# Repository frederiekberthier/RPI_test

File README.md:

# Raspberry Pi testsoftware
Test library om RPI hardwarematig te testen

## Opstelling
- **TEST-SERVER** (eigen Pi 5, met scherm): stuurt de test aan en maakt het rapport.
- **TEST-CLIENT** (de te testen Pi 4/5): bootet van een eigen TEST-CLIENT-SD met de agent.
- Verbonden met: GPIO-adapter (alleen GND + GPIO's, met serieweerstanden, géén 5V/3V3) en een
  rechtstreekse netwerkkabel met statische IP's. De GPIO-adapter kan op breadboards ([docs/opstelling.md](docs/opstelling.md)) of als
  print met één koperlaag ([docs/pcb.md](docs/pcb.md)).

**Namen:** de twee Pi's heten **TEST-SERVER** en **TEST-CLIENT**. Aan de scripts geef je `server` of `client` mee
(`./install.sh server`); de hostnamen worden `test-server` en `test-client`. De namen gaan over de Pi's, niet over het
netwerkprotocol: de agent op de TEST-CLIENT is technisch een HTTP-server en de TEST-SERVER roept hem aan.
"Raspberry Pi tester" is de naam van de applicatie.

## Installeren op een Pi: stappenplan
Eén script (`install.sh`) doet alles: voorcontrole, pakketten (`apt`), software, hostnaam, vrije GPIO-pinnen, wifi-land,
scherm met kiosk (TEST-SERVER), dienst en het vaste IP-adres. Het controleert per onderdeel eerst of het er al staat, dus je
kunt het veilig opnieuw uitvoeren. De stappen zijn voor de TEST-SERVER en de TEST-CLIENT-SD hetzelfde; alleen `server` of `client` verschilt.

1. **Schrijf Raspberry Pi OS Trixie (64-bit)** naar een SD-kaart met Raspberry Pi Imager: *met bureaublad* voor de TEST-SERVER,
   *Lite* voor de TEST-CLIENT-SD. Stel in de Imager een gebruiker, wifi (land `BE`) en SSH in.
2. **Start de Pi met internet** (via wifi, niet via de ethernetpoort die de testkabel wordt) en haal de software binnen:
   ```
   sudo apt install -y git
   git clone https://github.com/frederiekberthier/RPI_test.git
   cd RPI_test
   ```
3. **Kijk wat er al op de Pi staat** (optioneel, wijzigt niets):
   ```
   sudo ./install.sh server --check        # of: client
   ```
4. **Installeer** (voor het eerst ca. 5 tot 10 minuten):
   ```
   sudo ./install.sh server                # of: client
   ```
   Het script doet eerst een voorcontrole en stopt met een duidelijke melding als er iets ontbreekt.
5. **Herstart:** `sudo reboot`
6. **Controleer het resultaat:** `sudo ./image/verify.sh server` (of `client`)
7. **Iets mis?** `sudo ./image/diagnose.sh` verzamelt alle relevante uitvoer in één bestand om te delen.

| Optie | Wat het doet |
|---|---|
| `--check` | toont per onderdeel *aanwezig*, *ontbreekt* of *onbekend*; wijzigt niets |
| `--force` | past alles opnieuw toe, ook wat al aanwezig lijkt |
| `--readonly` | (alleen `client`) maakt het bestandssysteem alleen-lezen na de installatie |
| `--skip-preflight` | slaat de voorcontrole over |

**Bijwerken** naar een nieuwe versie: `git pull && sudo ./install.sh server`. Het script ziet dat alleen de software
verouderd is, vervangt die en herstart de dienst; de rest wordt overgeslagen.

Meer: [docs/eerste-installatie.md](docs/eerste-installatie.md) (draaiboek voor de eerste keer, met controlelijst),
[docs/image.md](docs/image.md) (scherm, diensten, SD klonen, probleemoplossing) en
[docs/opstelling.md](docs/opstelling.md) (onderdelen en bedrading van het breadboard).

## Ontwikkelen zonder hardware
```
pip install -e .[dev]
python -m pytest
python -m rpitest --mock                                   # gezonde gesimuleerde Pi
python -m rpitest.ui --mock                                # het scherm van de TEST-SERVER, op http://127.0.0.1:8080
python -m rpitest --mock --fault stuck_low:C:5 --fault bridge:C:10:11 --fault open:7
python -m rpitest --mock --fault eth_100 --fault wifi_5g_dead --fault bt_client_tx_dead
```
Faalspecificaties: `stuck_low|stuck_high:<S|C>:<pin>`, `bridge:<S|C>:<a>:<b>`, `open:<pin>`.
Systeemfouten: `eth_100`, `eth_errors`, `eth_slow`, `eth_loss`, `no_wifi`, `wifi_5g_dead`, `wifi_weak`,
`no_bt`, `bt_client_rx_dead`, `bt_client_tx_dead`, `server_no_wifi`, `server_no_bt`,
`usb_slotN_dead|usb2|corrupt|slow` (N = 1..4), `usb_no_sticks`, `usb_overcurrent`, `usb_disconnect`,
`power_undervolt`, `power_undervolt_history`, `power_hot`, `power_warm`, `power_throttle`, `power_cpu_error`,
`power_ram_error`, `power_core_missing`, `power_no_sensor`, `power_dip`, `power_throttle_blip`.

## Stand van zaken
Klaar: skelet, agent (JSON-RPC over HTTP), mock met foutinjectie, GPIO-checks, JSON/HTML-rapport,
echte GPIO-backend (libgpiod 2.x, enkel getest met een nep-`gpiod`), bedradingshandleiding,
netwerk-, wifi-, bluetooth-, USB- en voeding/temperatuurchecks (alleen getest met simulatie en nagebootste tooluitvoer).
Scherm met startknop en live resultaten (`rpitest.ui`), en één installatiescript voor server en TEST-CLIENT (`install.sh`),
getest tegen nagebootste systeemopdrachten.
Nog te doen: alles op echte Pi's bevestigen (ook het installatiescript).

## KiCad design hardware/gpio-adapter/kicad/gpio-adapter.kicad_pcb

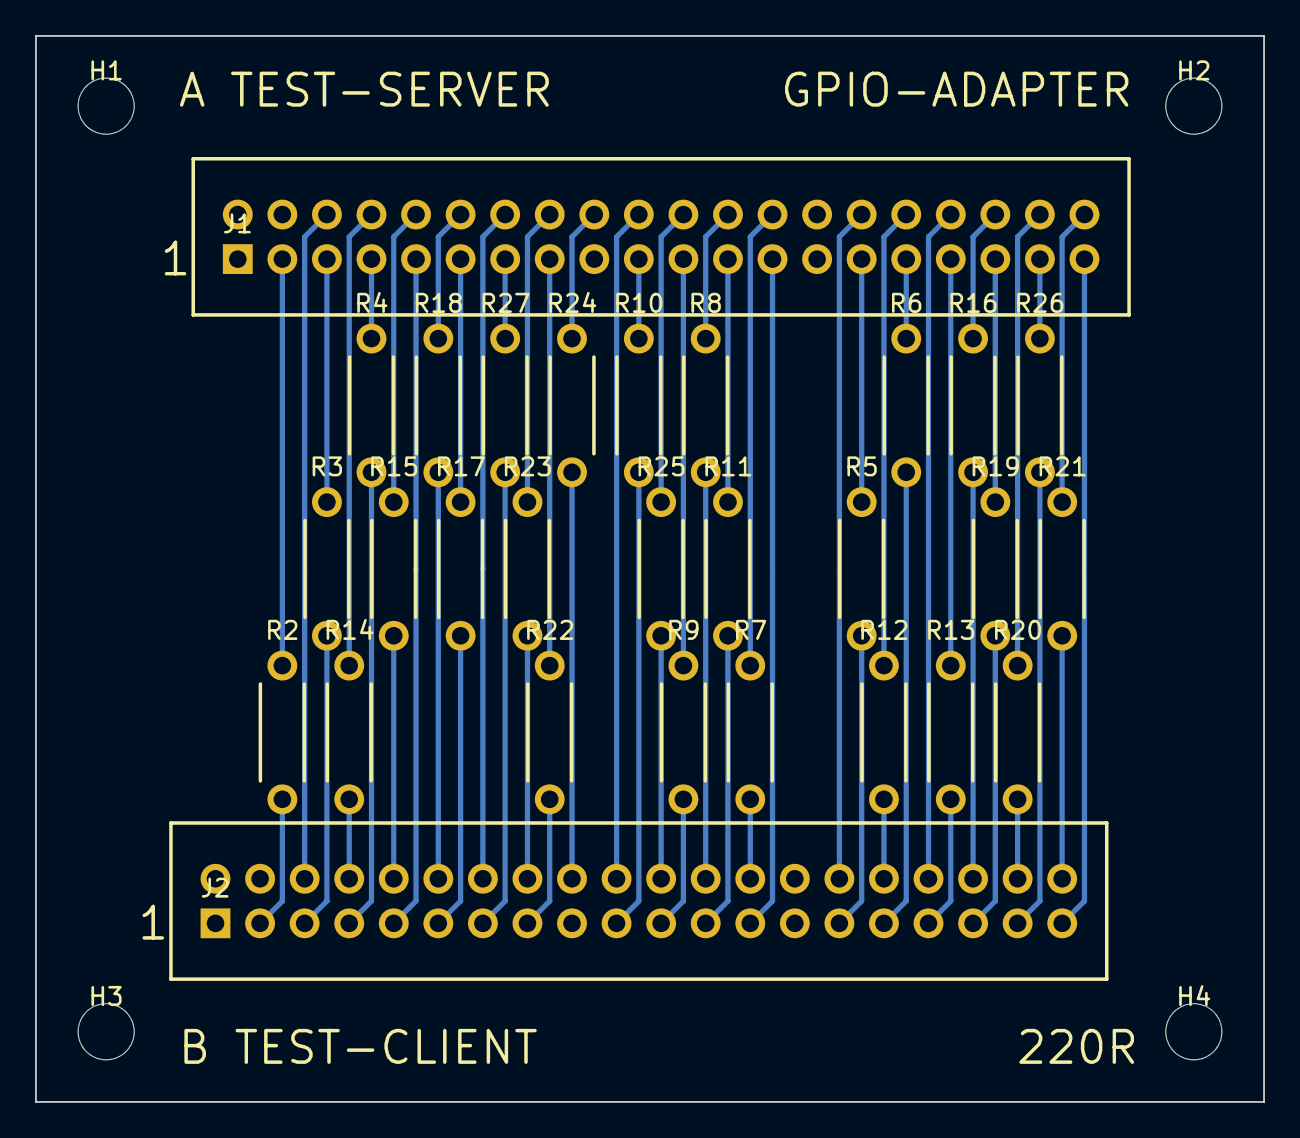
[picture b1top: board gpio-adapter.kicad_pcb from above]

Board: 2 copper layers, 70.0 x 60.8 mm, 32 parts (0 on the bottom side), 53 nets.

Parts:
H1, H2, H3, H4: M3; MountingHole_3.2mm_M3
J1, J2: 2x20; IDC-Header_2x20_P2.54mm_Horizontal_Mirrored
R2, R3, R4, R5, R6, R7, R8, R9, R10, R11, R12, R13, R14, R15, R16, R17, R18, R19, R20, R21, R22, R23, R24, R25, R26, R27: 220; R_Axial_DIN0207_L6.3mm_D2.5mm_P7.62mm

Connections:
GND: J1.6, J1.9, J1.14, J1.20, J1.25, J1.30, J1.34, J1.39, J2.6, J2.9, J2.14, J2.20, J2.25, J2.30, J2.34, J2.39
GPIO2_A: J1.3, R2.1
GPIO2_B: J2.3, R2.2
GPIO3_A: J1.5, R3.1
GPIO3_B: J2.5, R3.2
GPIO4_A: J1.7, R4.1
GPIO4_B: J2.7, R4.2
GPIO5_A: J1.29, R5.1
GPIO5_B: J2.29, R5.2
GPIO6_A: J1.31, R6.1
GPIO6_B: J2.31, R6.2
GPIO7_A: J1.26, R7.1
GPIO7_B: J2.26, R7.2
GPIO8_A: J1.24, R8.1
GPIO8_B: J2.24, R8.2
GPIO9_A: J1.21, R9.1
GPIO9_B: J2.21, R9.2
GPIO10_A: J1.19, R10.1
GPIO10_B: J2.19, R10.2
GPIO11_A: J1.23, R11.1
GPIO11_B: J2.23, R11.2
GPIO12_A: J1.32, R12.1
GPIO12_B: J2.32, R12.2
GPIO13_A: J1.33, R13.1
GPIO13_B: J2.33, R13.2
GPIO14_A: J1.8, R14.1
GPIO14_B: J2.8, R14.2
GPIO15_A: J1.10, R15.1
GPIO15_B: J2.10, R15.2
GPIO16_A: J1.36, R16.1
GPIO16_B: J2.36, R16.2
GPIO17_A: J1.11, R17.1
GPIO17_B: J2.11, R17.2
GPIO18_A: J1.12, R18.1
GPIO18_B: J2.12, R18.2
GPIO19_A: J1.35, R19.1
GPIO19_B: J2.35, R19.2
GPIO20_A: J1.38, R20.1
GPIO20_B: J2.38, R20.2
GPIO21_A: J1.40, R21.1
GPIO21_B: J2.40, R21.2
GPIO22_A: J1.15, R22.1
GPIO22_B: J2.15, R22.2
GPIO23_A: J1.16, R23.1
GPIO23_B: J2.16, R23.2
GPIO24_A: J1.18, R24.1
GPIO24_B: J2.18, R24.2
GPIO25_A: J1.22, R25.1
GPIO25_B: J2.22, R25.2
GPIO26_A: J1.37, R26.1
GPIO26_B: J2.37, R26.2
GPIO27_A: J1.13, R27.1
GPIO27_B: J2.13, R27.2

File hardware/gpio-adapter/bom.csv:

Aantal,Referenties,Waarde,Onderdeel,Opmerking
26,R2 R3 R4 R5 R6 R7 R8 R9 R10 R11 R12 R13 R14 R15 R16 R17 R18 R19 R20 R21 R22 R23 R24 R25 R26 R27,220 ohm,"weerstand axiaal 0,25 W, 5 % of beter, DIN0207, steek 7,62 mm",één per GPIO-lijn
2,J1 J2,2x20,"boxheader (shrouded IDC) 2x20, 2,54 mm, recht, soldeer","J1 = TEST-SERVER, J2 = TEST-CLIENT"
2,,40-polig,"lintkabel met twee IDC-connectoren (zoals voor de GPIO van een Pi), 1:1",één per Pi; niet kruisen of draaien
4,H1 H2 H3 H4,M3,afstandsbusje of schroef,"optioneel, voor montage"
